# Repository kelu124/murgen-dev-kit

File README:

# Instructions to get a clean repo :

https://gist.github.com/chrisjacob/833223

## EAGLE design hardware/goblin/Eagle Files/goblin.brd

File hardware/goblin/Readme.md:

# What ?
A bonus to [Murgen](https://github.com/echopen/hardware/tree/master/electronics/murgen)

Goblin was originally an alternative version of Murgen, shifted it to a separate product to make some space - a goodies of sorts =)

# People ! 
## Acknowledgement

Murgen, Sofian, Amit, Emmanuel, Florent, Bertrand & PHH, Mike in a way, list goes on !

# License

Licensed under TAPR Open Hardware License (www.tapr.org/OHL)

Copyright Murgen and Kelu124 (murgen@echopen.org , luc@echopen.org) 2015-2016

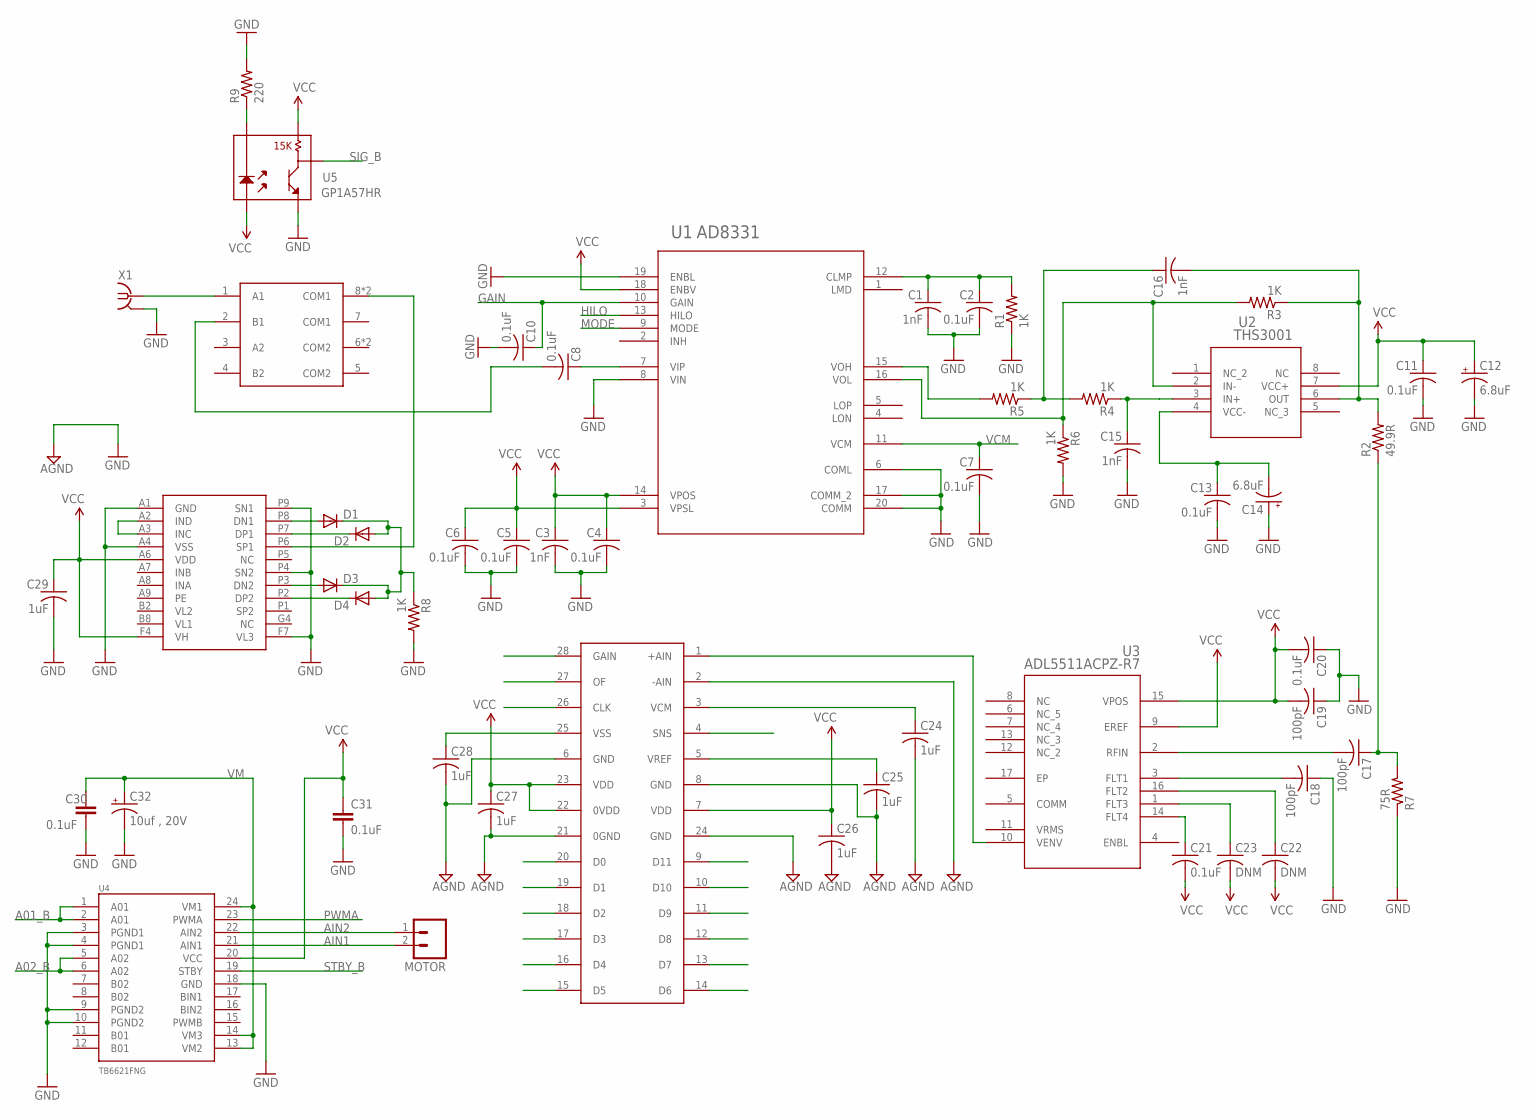
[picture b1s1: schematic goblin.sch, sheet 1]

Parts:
C1, C3, C15, C16: 1nF; C0402
C2, C4, C5, C6, C7, C8, C10, C11, C13, C20, C21: 0.1uF; C0402
C12, C14: 6.8uF; A/3216-18W
C17, C18, C19: 100pF; C0402
C22, C23: DNM; C0402
C24, C25, C26, C27, C28, C29: 1uF; C0402
C30, C31: 0.1uF; 0402-CAP
C32: 10uf , 20V; EIA3528
D1, D2, D3, D4: DIODESOD; SOD-323
MOTOR: M02PTH3; 1X02_LONGPADS
R1, R3, R4, R5, R6, R8: 1K; R0402
R2: 49.9R; R0402
R7: 75R; R0402
R9: 220; AXIAL-0.3
U1: AD8331; RQ_20
U2: THS3001; D8
U3: ADL5511ACPZ-R7; CP_16_22
U4: TB6621FNG; SSOP24
U5: GP1A57HR
U6: MDO100
U7: LT3748; LT3768
U8: LTC1405
X1: SMA-142-0701-871/880; SMA-142-0701-871

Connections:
A01_B: U4.1 (A01), U4.2 (A01); also elsewhere on the board
A02_B: U4.5 (A02), U4.6 (A02); also elsewhere on the board
AGND: C24.2, C25.2, C26.2, C27.2, C28.2, U8.2 (-AIN), U8.6 (GND), U8.8 (GND), U8.21 (0GND), U8.24 (GND); also elsewhere on the board
AIN1: MOTOR.2, U4.21 (AIN1)
AIN2: MOTOR.1, U4.22 (AIN2)
CLK: U8.26 (CLK); also elsewhere on the board
D0: U8.20 (D0); also elsewhere on the board
D1: U8.19 (D1); also elsewhere on the board
D2: U8.18 (D2); also elsewhere on the board
D3: U8.17 (D3); also elsewhere on the board
D4: U8.16 (D4); also elsewhere on the board
D5: U8.15 (D5); also elsewhere on the board
D6: U8.14 (D6); also elsewhere on the board
D7: U8.13 (D7); also elsewhere on the board
D8: U8.12 (D8); also elsewhere on the board
D9: U8.11 (D9); also elsewhere on the board
D10: U8.10 (D10); also elsewhere on the board
D11: U8.9 (D11); also elsewhere on the board
GAIN: C10.1, U1.10 (GAIN)
GAIN_ADC_B: U8.28 (GAIN); also elsewhere on the board
GND: C1.2, C2.2, C3.2, C4.2, C5.2, C6.2, C7.2, C10.2, C11.2, C12.-, C13.2, C14.+, C15.2, C18.1, C19.1, C20.1, C29.2, C30.2, C31.2, C32.C (-), R1.1, R6.2, R7.1, R8.2, R9.P$2 (2), U1.6 (COML), U1.8 (VIN), U1.17 (COMM_2), U1.19 (ENBL), U1.20 (COMM), U4.3 (PGND1), U4.4 (PGND1), U4.9 (PGND2), U4.10 (PGND2), U4.18 (GND), U5.5, U7.A1 (GND), U7.A4 (VSS), U7.F7 (VL3), U7.P4 (SN2), U7.P9 (SN1), X1.2@1 (2), X1.2@2 (2), X1.2@3 (2), X1.2@4 (2); also elsewhere on the board
HILO: U1.13 (HILO)
MODE: U1.9 (MODE)
unnamed: U6.1 (A1), X1.1
unnamed: C1.1, C2.1, R1.2, U1.12 (CLMP)
unnamed: C8.1, U1.7 (VIP)
unnamed: C13.1, C14.-, U2.4 (VCC-)
unnamed: C8.2, U6.2 (B1)
unnamed: C16.2, R2.2, R3.1, U2.6 (OUT)
unnamed: R3.2, R6.1, U1.16 (VOL), U2.2 (IN-)
unnamed: R5.2, U1.15 (VOH)
unnamed: C17.2, U3.2 (RFIN)
unnamed: C18.2, U3.3 (FLT1)
unnamed: C17.1, R2.1, R7.2
unnamed: C16.1, R4.2, R5.1
unnamed: C15.1, R4.1, U2.3 (IN+)
unnamed: U6.8 (COM1), U6.9 (COM1), U7.P6 (SP1)
unnamed: C21.1, U3.14 (FLT4)
unnamed: C22.1, U3.16 (FLT2)
unnamed: C23.1, U3.1 (FLT3)
unnamed: C24.1, U8.3 (VCM)
unnamed: C25.1, U8.5 (VREF)
unnamed: U7.A2 (IND), U7.A3 (INC)
unnamed: D1.2 (A), U7.P8 (DN1)
unnamed: C28.1, U8.25 (VSS)
unnamed: D2.1 (C), U7.P7 (DP1)
unnamed: U3.10 (VENV), U8.1 (+AIN)
unnamed: D3.2 (A), U7.P3 (DN2)
unnamed: D4.1 (C), U7.P2 (DP2)
unnamed: D1.1 (C), D2.2 (A), D3.1 (C), D4.2 (A), R8.1
unnamed: R9.P$1 (1), U5.2
OF_B: U8.27 (OF); also elsewhere on the board
PWMA: U4.23 (PWMA); also elsewhere on the board
SIG_B: U5.4; also elsewhere on the board
SNS_B: U8.4 (SNS); also elsewhere on the board
STBY_B: U4.19 (STBY); also elsewhere on the board
VCC: C3.1, C4.1, C5.1, C6.1, C11.1, C12.+, C19.2, C20.2, C21.2, C22.2, C23.2, C26.1, C27.1, C29.1, C31.1, U1.3 (VPSL), U1.14 (VPOS), U1.18 (ENBV), U2.7 (VCC+), U3.9 (EREF), U3.15 (VPOS), U4.20 (VCC), U5.1, U5.3, U7.A6 (VDD), U7.F4 (VH), U8.7 (VDD), U8.22 (0VDD), U8.23 (VDD); also elsewhere on the board
VCM: C7.1, U1.11 (VCM)
VM: C30.1, C32.A (+), U4.13 (VM2), U4.14 (VM3), U4.24 (VM1)

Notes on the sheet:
VCM
HILO
MODE
GAIN

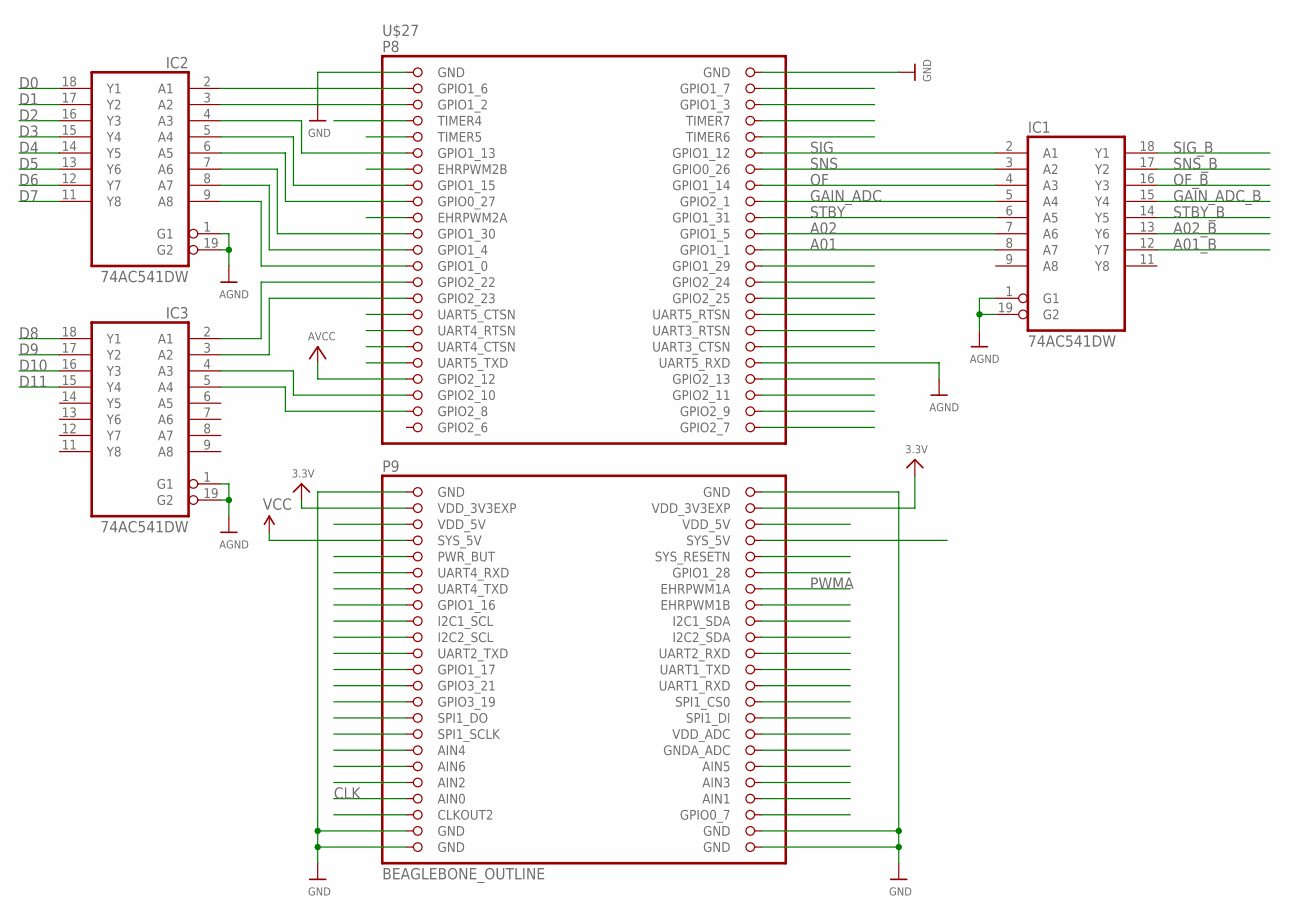
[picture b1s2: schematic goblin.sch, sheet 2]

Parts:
IC1, IC2, IC3: 74AC541DW; SO20W
U$27: BEAGLEBONE_OUTLINE; BEAGLEBONE_SHIELD

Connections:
3.3V: U$27.49 (VDD_3V3EXP), U$27.50 (VDD_3V3EXP)
5.0V: U$27.54 (SYS_5V)
A01_B: IC1.12 (Y7); also elsewhere on the board
A02: IC1.8 (A7), U$27.24 (GPIO1_1)
A02_B: IC1.13 (Y6); also elsewhere on the board
AGND: IC1.1 (G1), IC1.19 (G2), IC2.1 (G1), IC2.19 (G2), IC3.1 (G1), IC3.19 (G2), U$27.38 (UART5_RXD); also elsewhere on the board
AVCC: U$27.39 (GPIO2_12)
CLK: U$27.87 (CLKOUT2); also elsewhere on the board
D0: IC2.18 (Y1); also elsewhere on the board
D1: IC2.17 (Y2); also elsewhere on the board
D2: IC2.16 (Y3); also elsewhere on the board
D3: IC2.15 (Y4); also elsewhere on the board
D4: IC2.14 (Y5); also elsewhere on the board
D5: IC2.13 (Y6); also elsewhere on the board
D6: IC2.12 (Y7); also elsewhere on the board
D7: IC2.11 (Y8); also elsewhere on the board
D8: IC3.18 (Y1); also elsewhere on the board
D9: IC3.17 (Y2); also elsewhere on the board
D10: IC3.16 (Y3); also elsewhere on the board
D11: IC3.15 (Y4); also elsewhere on the board
GAIN_ADC: IC1.5 (A4), U$27.18 (GPIO2_1)
GAIN_ADC_B: IC1.15 (Y4); also elsewhere on the board
GND: IC1.10 (GND), IC2.10 (GND), IC3.10 (GND), U$27.1 (GND), U$27.2 (GND), U$27.47 (GND), U$27.48 (GND), U$27.89 (GND), U$27.90 (GND), U$27.91 (GND), U$27.92 (GND); also elsewhere on the board
GPIO2_6: U$27.45 (GPIO2_6)
unnamed: IC2.4 (A3), U$27.11 (GPIO1_13)
unnamed: IC2.6 (A5), U$27.17 (GPIO0_27)
unnamed: IC2.7 (A6), U$27.21 (GPIO1_30)
unnamed: IC2.8 (A7), U$27.23 (GPIO1_4)
unnamed: IC2.9 (A8), U$27.25 (GPIO1_0)
unnamed: IC3.2 (A1), U$27.27 (GPIO2_22)
unnamed: IC3.3 (A2), U$27.29 (GPIO2_23)
unnamed: IC3.4 (A3), U$27.41 (GPIO2_10)
unnamed: IC3.5 (A4), U$27.43 (GPIO2_8)
unnamed: IC1.7 (A6), U$27.22 (GPIO1_5)
unnamed: IC2.2 (A1), U$27.3 (GPIO1_6)
unnamed: IC2.3 (A2), U$27.5 (GPIO1_2)
OF: IC1.4 (A3), U$27.16 (GPIO1_14)
OF_B: IC1.16 (Y3); also elsewhere on the board
PWMA: U$27.60 (EHRPWM1A); also elsewhere on the board
SIG: IC1.2 (A1), U$27.12 (GPIO1_12)
SIG_B: IC1.18 (Y1); also elsewhere on the board
SNS: IC1.3 (A2), U$27.14 (GPIO0_26)
SNS_B: IC1.17 (Y2); also elsewhere on the board
STBY: IC1.6 (A5), U$27.20 (GPIO1_31)
STBY_B: IC1.14 (Y5); also elsewhere on the board
VCC: IC1.20 (VCC), IC2.20 (VCC), IC3.20 (VCC), U$27.53 (SYS_5V); also elsewhere on the board

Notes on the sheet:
A01
A02
STBY
PWMA
SNS
GAIN_ADC
CLK
SIG
A01_B
A02_B
STBY_B
GAIN_ADC_B
OF_B
SNS_B
SIG_B
D10
D11

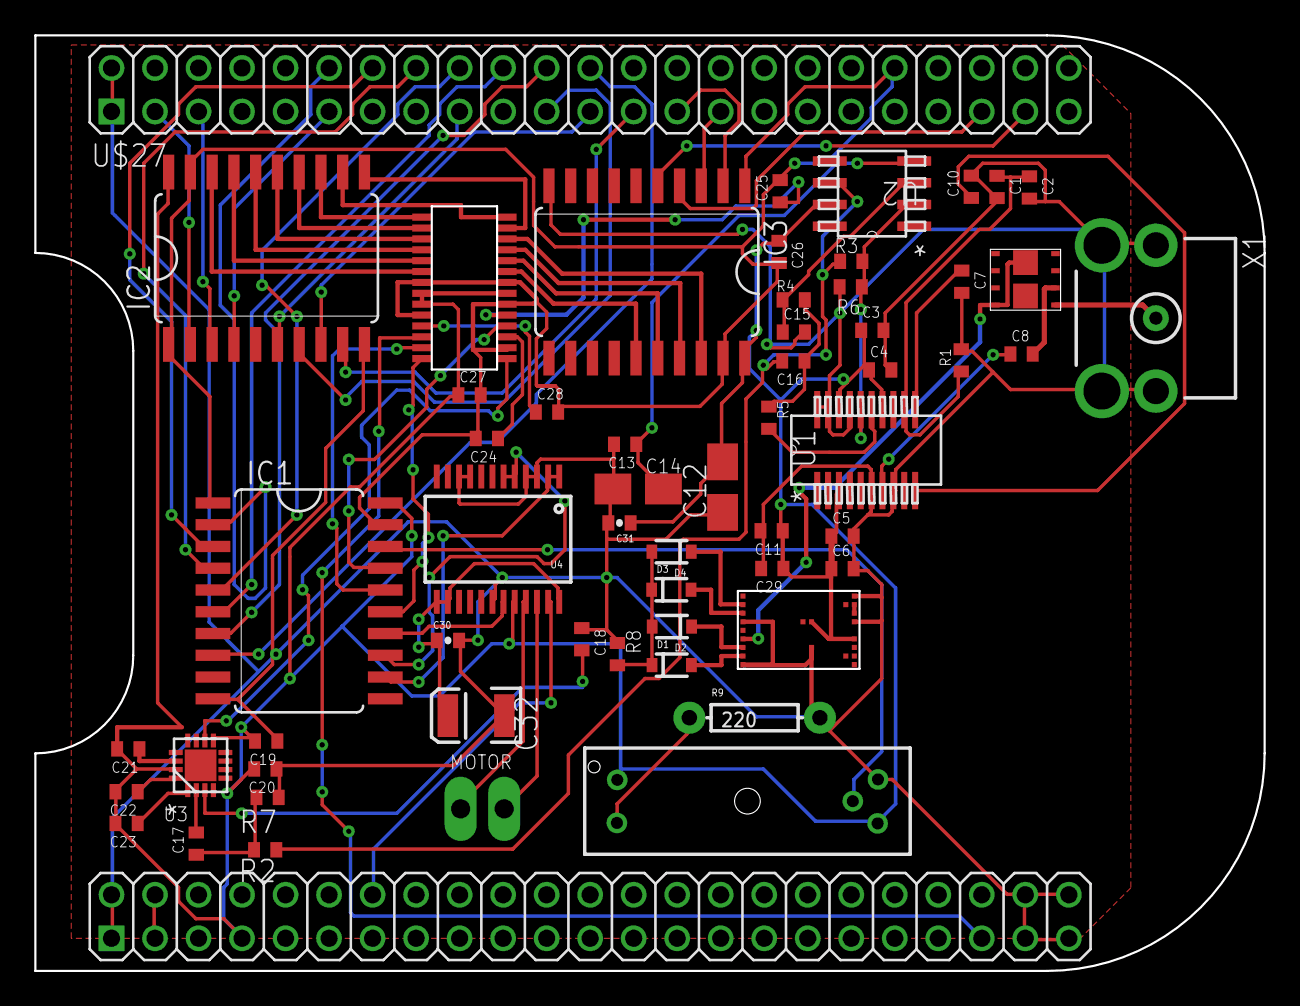
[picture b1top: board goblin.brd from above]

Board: 2 copper layers, 71.8 x 54.6 mm, 58 parts (0 on the bottom side), 76 nets.

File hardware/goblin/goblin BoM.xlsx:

|  | Item Name | Value | Package | Quantity | Manufacturer | Manufacturer Part# | Digikey Part#
 |  | C1,C3,C15 | 1nF | C0402 | 4 | Kemet | C0402C102K5RACTU | 399-1032-1-ND
 |  | C2,C4-C7,C8,C9,C11,C13,C18,C19,C20,C21,C30,C31 | 0.1uF | C0402 | 14 | Yageo | CC0402ZRY5V7BB104 | 311-1047-1-ND
 |  | C14 | 6.8uF | A/3216-18W | 2 | Kemet | T491A685M020AT | 399-4628-1-ND
 |  | C22 | DNM | C0402 | 2 | - | - | -
 |  | C24,C25,C26 | 1uF | C0402 | 6 | Yageo | CC0402KRX5R5BB105 | 311-1438-1-ND
 |  | C32 | 10uf , 20V | EIA3528 | 1 | Kemet | T491B106M020AT | 399-8300-1-ND
 |  | D1-D4 | Diode | SOD-323 | 4 | Fairchild Semiconductor | 1N4148WS | 1N4148WSFSCT-ND
 |  | R8 | 1K | R0402 | 1 | Yageo | AC0402FR-071KL | 311-1KLBCT-ND
 |  | R2 | 49.9R | R0402 | 1 | Yageo | RC0402FR-0749R9L | 311-49.9LRCT-ND
 |  | R1,R4,R5,R6,R8 | 1K | R0402 | 5 | Yageo | AC0402FR-071KL | 311-1KLBCT-ND
 |  | R7 | 75R | R0402 | 1 | Yageo | RC0402FR-0775RL | 311-75.0LRCT-ND
 |  | R9 | 220 | AXIAL-0.3 | 1 | Vishay BC Components | VR37000002205JR500 | PPCHHJ22MCT-ND
 |  | U1 | AD8331 | RQ_20 | 1 | Analog Devices Inc. | AD8331ARQZ-R7 | AD8331ARQZ-R7CT-ND
 |  | U2 | THS3001 | D8 | 1 | Texas Instruments | THS3001IDGNR | 296-12006-1-ND
 |  | U3 | ADL5511ACPZ-R7 | CP_16_22 | 1 | Analog Devices Inc. | ADL5511ACPZ-R7 | ADL5511ACPZ-R7CT-ND
 |  | U4 | TB6621FNG | SSOP24 | 1 | Toshiba Semiconductor and Storage | TB6612FNG,C,8,EL | TB6612FNGC8ELCT-ND
 |  | U5 | GP1A57HR | GP1A57HR | 1 | Sharp Microelectronics | GP1A57HRJ00F | 425-1935-5-ND
 |  | U6 | MDO100 | MDO100 | 1 | Microchip Technology | MD0100N8-G | MD0100N8-G-ND
 |  | U7 | LT3768 | LT3768 | 1 | Linear Technology | LT3748EMS#PBF | LT3748EMS#PBF-ND
 |  | U8 | LTC1405 | LTC1405 | 1 | Linear Technology | LTC1405IGN#PBF | LTC1405IGN#PBF-ND
 |  | X1 | SMA-142-0701-871/880 | SMA-142-0701-871 | 1 | Cinch Connectivity Solutions Johnson | 142-0701-871 | J610-ND
 |  | P8,P9 | BEAGLEBONE_OUTLINE | BEAGLEBONE_SHIELD | 2 | Sullins Connector Solutions | PRPC023DAAN-RC | S2011EC-23-ND

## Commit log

2016-02-19 Doc: update Readme, dumping bibliographie and MurgenNotes at the same time.
2016-02-19 Update of bibliographie
2016-02-21 Updating bibliographie and Readme - especially on HV
2016-02-25 Adding the 3D files and PDF of schematics in Readme.md
2016-02-26 Documentation for the Murgen short circuit
    Upload of images
2016-02-26 Documenting short issues and board debug
2016-03-03 Updating the wiki page backup
    Feb 27th to March 3rd
2016-03-04 Adding images for the doc
    Pictures of Murgen/BBB, and of the top silk screen for ease of mapping.
2016-03-06 Updating Session_1
2016-03-06 ReadMe & Session 1 update
2016-03-06 Correct typo
2016-03-06 Closing the Session_1 log
2016-03-06 Update Session1 bullets
2016-03-06 Sleeping
2016-03-09 Addition of 3D files and pictures
2016-03-10 Notes, tables & TODOS
2016-03-10 Updtodate
2016-03-11 Adding Session_2 draft
2016-03-11 Adding Session_2 draft v2
2016-03-11 Echoes detail in Session_2
2016-03-16 Session 3 updated
2016-03-16 Adding some pictures
2016-03-19 Nice 250ns pulses : session 4 added
2016-03-20 First 'real' ultrasound image
2016-03-20 Adding tofs, and correcting mistakes
2016-03-20 Minor typos in doc
2016-03-22 Creating ReadMe.murgen
    A summary of what has been done.
2016-03-22 Rename ReadMe.murgen to ReadMeMurgen.md
2016-03-22 Rename ReadMeMurgen.md to ReadMe.md
2016-03-22 Cleaning
2016-03-23 Different scan conversions
2016-03-28 Getting images from Fantoms
2016-03-29 Adding bigger images
2016-03-29 Adding images and comparison to the fantom
2016-03-29 Added files via upload
2016-03-29 ReadMe updated to reflect file structure
2016-04-01 Session 7: Images
2016-04-01 Cleaning images
2016-04-03 Adding latest files for dev-release
2016-04-03 Examples of code improvement
2016-04-03 Release cleaning ongoin
2016-04-03 Cleaning still
2016-04-03 Readme
2016-04-04 Commercial Grade Images ;)
2016-04-04 Cleaning the software
2016-04-04 Adding a 4-tap scan conversion
2016-04-04 Typos
2016-04-05 Cleaning for the bot
2016-04-05 Cleaning typos in ReadMe's
2016-04-05 Resizing images
2016-04-07 Doc & Images
2016-04-07 Some docs, starting with the doc/ folder
2016-04-10 Adding example files
2016-04-10 adding files
2016-04-13 Test metadata
2016-04-14 Closing documentation
2016-04-23 ReadmeLicense
2016-04-23 Create gh-pages branch via GitHub
2016-04-24 tofs
2016-05-01 Adding the fantoms specs
2016-05-01 Images for fantoms
2016-05-03 Comparing acquisition speeds
2016-05-04 Comparing images
2016-05-06 Comparing with raw images
2016-05-06 including image
2016-05-23 Adding pdfs
2016-06-03 Cleaning doc
2016-06-06 Cleaning from pages
2016-06-06 Cleaning gh-pages
2016-06-06 Adding Jekyll
2016-06-06 Repo
2016-06-06 Index
2016-06-06 First article
2016-06-06 About cleaned
2016-06-06 Resources
2016-06-08 Zach first session
2016-06-08 Completing Zach's
2016-06-09 Create 2016-06-09
2016-06-09 Add files via upload
    Here is a picture of my first echo (received June 9), and the set up that I got it from.
2016-06-13 Add files via upload
    June 13, 2016 work
2016-06-13 Tuto part II
2016-06-14 Adding CSVs files
2016-06-14 Adding the specs
2016-06-16 Old repo of Goblin and tobo removed
2016-06-20 Create 2016-06-20
2016-06-21 Scan conversion for images taken with Murgen board
    Data from the Murgen board was collected in MATLAB, but the code for
    scan conversion is in Python.
    Noise reduction was done by returning the absolute value of the output
    to remove negative noise and then a log greyscale was implemented.
2016-06-22 Part III, getting images
2016-06-22 Adding link to repo
2016-06-22 Link to tuto
2016-06-23 June 22, 2016
    Today I got the Beaglebone to pulse the the Murgen board to get images
    (Gain voltage of 0.7V and current of 0.086A). Beaglebone sends the
    positive and negative pulses from P9_22 and 21 respectively. I worked
    on the software side of image processing, implementing a high pass
    filter, hilbert transformation, and scan conversion. Data, codes, and
    images are included.
2016-06-24 Echoes at various TPs
    I went through various TPs today, measuring between them to try to see
    how the signal was processed by the Murgen board. I was expecting an
    envelope at TP8, but it only seemed to give me the same signal as
    between TP2 and TP3, but with less gain.
2016-06-24 TP echoes 2
    Those same TP echoes as before, but at different screen settings to see
    the entire pulse, not just the echo
2016-06-24 Adding Zach's insights
2016-06-24 Zach 22/06
2016-06-25 Removing the filter part for murgen
2016-07-03 Playing with ATL 10PV
2016-07-03 Arty moment
2016-07-03 Adding 10PV
2016-07-05 Adding echoes from ATL 10PV using echopen's homemade analog processing chain
2016-07-07 Adding TP2 and TP7 comparison
2016-07-07 Direct link to data
2016-07-07 Reorg Zach's work
2016-07-07 Adding Zach's patch-1 branch
2016-07-26 New test of probes
2016-07-26 Images with rotating ATLs
2016-08-02 Pic of shorting the filter
2016-08-24 Zach setup
2016-08-26 Adding logo
2016-09-06 Examples edit
2016-09-15 Minor formatting fix in hardware/Readme.md
    To make the hardware directories line up better, use Markdown's preformat mode.
2016-10-19 Adding notes
2016-10-19 Cleaning the notes
2016-11-01 Added repo from computer
2016-11-01 test
2016-11-01 test
    test
2017-08-09 Cleaning addresses
2021-11-11 Update of readme

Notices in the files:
parts and their libraries:
SparkFun-DiscreteSemi: Licensing: CC v3.0 Share-Alike You are welcome to use this library for commercial purposes.
